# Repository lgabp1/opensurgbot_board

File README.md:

# opensurgbot_board

Submodule of [opensurgbot](https://github.com/lgabp1/opensurgbot).

Board design for the opensurgbot first prototype.

## About

The opensurgbot was temporarily named _deehli_, and the board design has not been updated since the name change. Thus, the kicad files and the board name still refer to _deehli_.

## Known issues (vB-1.03)
- Several trace connections were forgotten in version vB-1.03

## Versions
### v0.1

### v1.0

### v1.02

### vB-1.01

### vB-1.03

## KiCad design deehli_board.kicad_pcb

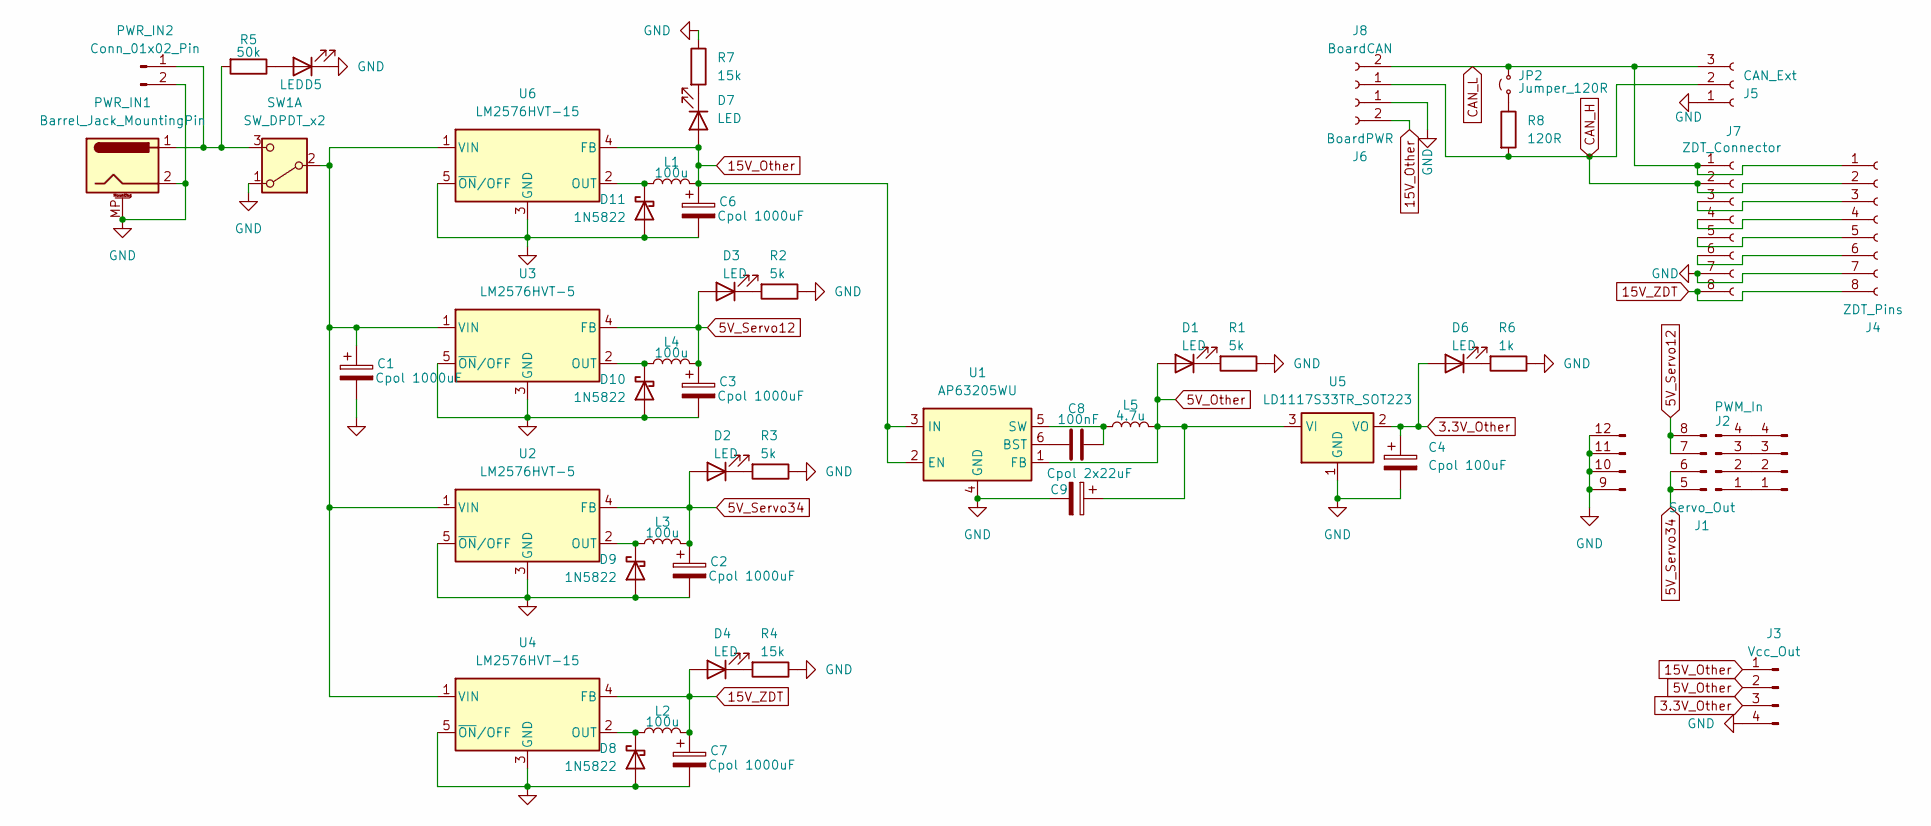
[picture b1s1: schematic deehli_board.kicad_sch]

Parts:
C1, C2, C3, C6, C7: Cpol 1000uF; CP_Radial_D10.0mm_P5.00mm
C4: Cpol 100uF; CP_Radial_D6.3mm_P2.50mm
C8: 100nF; C_0805_2012Metric_Pad1.18x1.45mm_HandSolder
C9: Cpol 2x22uF; CP_Radial_D6.3mm_P2.50mm
D1, D2, D3, D4, D5, D6, D7: LED; LED_0805_2012Metric_Pad1.15x1.40mm_HandSolder
D8, D9, D10, D11: 1N5822; D_DO-201AD_P15.24mm_Horizontal
J1: Servo_Out; PinHeader_3x04_P2.54mm_Vertical
J2: PWM_In; PinHeader_1x04_P2.54mm_Vertical
J3: Vcc_Out; PinSocket_1x04_P2.54mm_Vertical
J4: ZDT_Pins; PinSocket_1x08_P2.54mm_Horizontal
J5: CAN_Ext; TerminalBlock_Xinya_XY308-2.54-3P_1x03_P2.54mm_Horizontal
J6: BoardPWR; TerminalBlock_Xinya_XY308-2.54-2P_1x02_P2.54mm_Horizontal
J7: ZDT_Connector; JST_EH_S8B-EH_1x08_P2.50mm_Horizontal
J8: BoardCAN; TerminalBlock_Xinya_XY308-2.54-2P_1x02_P2.54mm_Horizontal
JP2: Jumper_120R; PinHeader_1x02_P2.54mm_Vertical
L1, L2, L3, L4: 100u; L_Radial_D8.7mm_P5.00mm_Fastron_07HCP
L5: 4.7u; L_Radial_D8.7mm_P5.00mm_Fastron_07HCP
PWR_IN1: Barrel_Jack_MountingPin; BarrelJack_CUI_PJ-063AH_Horizontal
PWR_IN2: Conn_01x02_Pin; PinHeader_1x02_P2.54mm_Vertical
R1, R2, R3: 5k; R_0805_2012Metric_Pad1.20x1.40mm_HandSolder
R4, R7: 15k; R_0805_2012Metric_Pad1.20x1.40mm_HandSolder
R5: 50k; R_0805_2012Metric_Pad1.20x1.40mm_HandSolder
R6: 1k; R_0805_2012Metric_Pad1.20x1.40mm_HandSolder
R8: 120R; R_0805_2012Metric_Pad1.20x1.40mm_HandSolder
SW1: SW_DPDT_x2; SW_Toggle_Blue_wSlots
U1: AP63205WU; TSOT-23-6
U2, U3: LM2576HVT-5; TO-220-5_Vertical
U4, U6: LM2576HVT-15; TO-220-5_Vertical
U5: LD1117S33TR_SOT223; SOT-223-3_TabPin2

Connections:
3.3V_Other: C4.1, D6.2 (A), J3.3, U5.2 (VO)
5V_Other: C9.1, D1.2 (A), J3.2, L5.2, U1.1 (FB), U5.3 (VI)
5V_Servo12: C3.1, D3.2 (A), J1.7, J1.8, L4.2, U3.4 (FB)
5V_Servo34: C2.1, D2.2 (A), J1.5, J1.6, L3.2, U2.4 (FB)
15V_Other: C6.1, D7.2 (A), J3.1, J6.2, L1.2, U1.2 (EN), U1.3 (IN), U6.4 (FB)
15V_ZDT: C7.1, D4.2 (A), J4.8, J7.8, L2.2, U4.4 (FB)
CAN_H: J4.2, J5.2, J7.2, J8.1, R8.2
CAN_L: J4.1, J5.3, J7.1, J8.2, JP2.2 (B)
GND: C1.2, C2.2, C3.2, C4.2, C6.2, C7.2, C9.2, D5.1 (K), D8.2 (A), D9.2 (A), D10.2 (A), D11.2 (A), J1.9, J1.10, J1.11, J1.12, J3.4, J4.7, J5.1, J6.1, J7.7, PWR_IN1.2, PWR_IN1.MP (MountPin), PWR_IN2.2, R1.1, R2.1, R3.1, R4.1, R6.1, R7.1, SW1.1 (A), U1.4 (GND), U2.3 (GND), U2.5 (~ON/OFF), U3.3 (GND), U3.5 (~ON/OFF), U4.3 (GND), U4.5 (~ON/OFF), U5.1 (GND), U6.3 (GND), U6.5 (~ON/OFF)
unnamed: D1.1 (K), R1.2
unnamed: D2.1 (K), R3.2
unnamed: D3.1 (K), R2.2
unnamed: D4.1 (K), R4.2
unnamed: D5.2 (A), R5.1
unnamed: D6.1 (K), R6.2
unnamed: D7.1 (K), R7.2
unnamed: D8.1 (K), L2.1, U4.2 (OUT)
unnamed: D9.1 (K), L3.1, U2.2 (OUT)
unnamed: D10.1 (K), L4.1, U3.2 (OUT)
unnamed: D11.1 (K), L1.1, U6.2 (OUT)
unnamed: J1.1, J2.1
unnamed: J1.2, J2.2
unnamed: J1.3, J2.3
unnamed: J1.4, J2.4
unnamed: J4.3, J7.3
unnamed: J4.4, J7.4
unnamed: J4.5, J7.5
unnamed: J4.6, J7.6
unnamed: JP2.1 (A), R8.1
unnamed: PWR_IN1.1, PWR_IN2.1, R5.2, SW1.3 (C)
unnamed: C1.1, SW1.2 (B), U2.1 (VIN), U3.1 (VIN), U4.1 (VIN), U6.1 (VIN)
unnamed: C8.1, U1.6 (BST)
unnamed: C8.2, L5.1, U1.5 (SW)

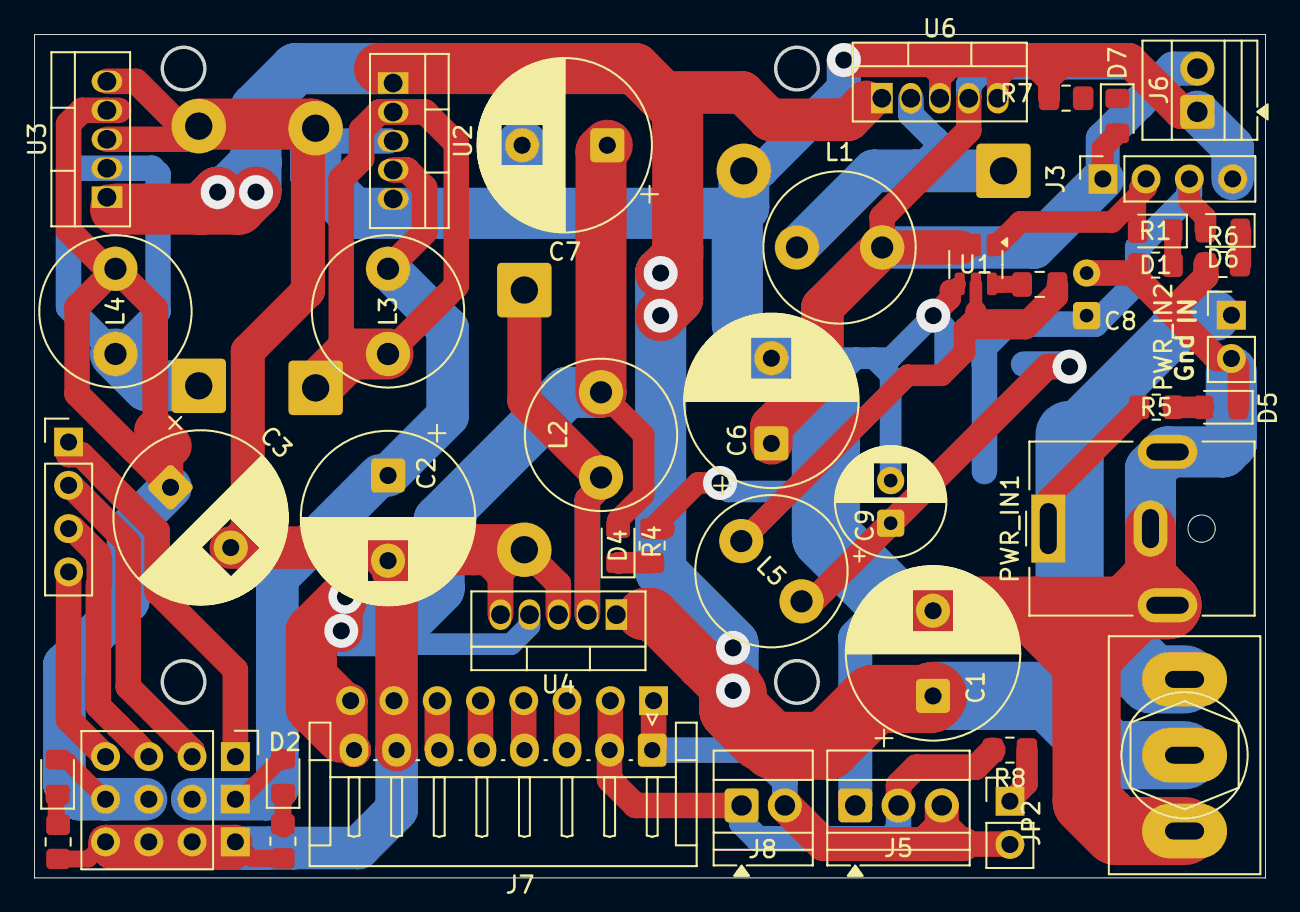
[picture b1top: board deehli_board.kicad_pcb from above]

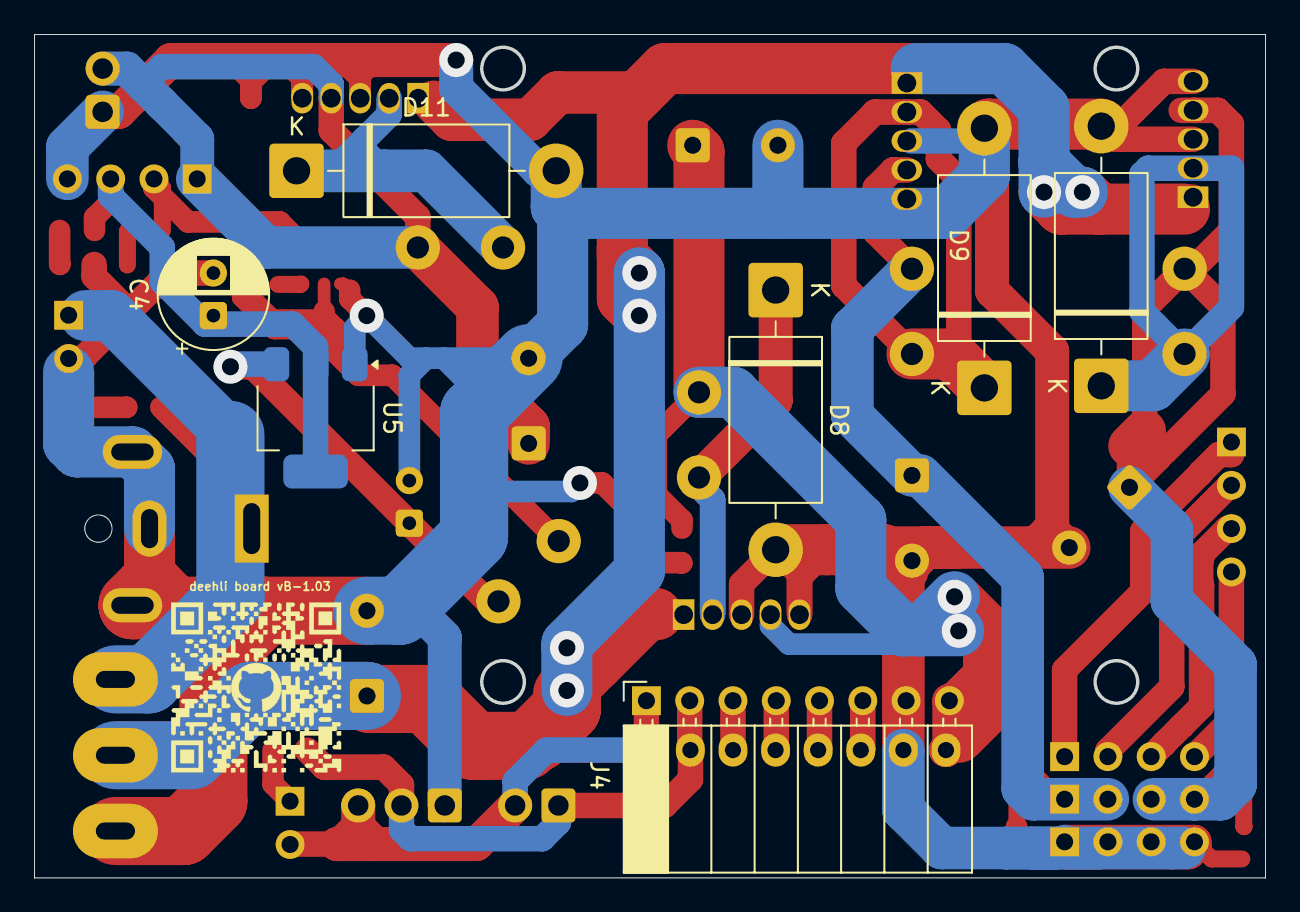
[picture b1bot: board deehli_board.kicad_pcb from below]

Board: 2 copper layers, 72.2 x 49.5 mm, 50 parts (7 on the bottom side), 33 nets.

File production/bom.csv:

Designator,Footprint,Quantity,Value,LCSC Part #
"C1, C2, C3, C6, C7",CP_Radial_D10.0mm_P5.00mm,5,Cpol 1000uF,
C4,CP_Radial_D6.3mm_P2.50mm,1,Cpol 100uF,
C8,0805,1,100nF,
C9,CP_Radial_D6.3mm_P2.50mm,1,Cpol 2x22uF,
"D1, D2, D3, D4, D5, D6, D7",0805,7,LED,
"D10, D11, D8, D9",D_DO-201AD_P15.24mm_Horizontal,4,1N5822,
J1,PinHeader_3x04_P2.54mm_Vertical,1,Servo_Out,
J2,PinHeader_1x04_P2.54mm_Vertical,1,PWM_In,
J3,PinSocket_1x04_P2.54mm_Vertical,1,Vcc_Out,
J4,PinSocket_1x08_P2.54mm_Horizontal,1,ZDT_Pins,
J5,TerminalBlock_Xinya_XY308-2.54-3P_1x03_P2.54mm_Horizontal,1,CAN_Ext,
J6,TerminalBlock_Xinya_XY308-2.54-2P_1x02_P2.54mm_Horizontal,1,BoardPWR,
J7,JST_EH_S8B-EH_1x08_P2.50mm_Horizontal,1,ZDT_Connector,
J8,TerminalBlock_Xinya_XY308-2.54-2P_1x02_P2.54mm_Horizontal,1,BoardCAN,
JP2,PinHeader_1x02_P2.54mm_Vertical,1,Jumper_120R,
"L1, L2, L3, L4",L_Radial_D8.7mm_P5.00mm_Fastron_07HCP,4,100u,
L5,L_Radial_D8.7mm_P5.00mm_Fastron_07HCP,1,4.7u,
PWR_IN1,BarrelJack_CUI_PJ-063AH_Horizontal,1,Barrel_Jack_MountingPin,
PWR_IN2,PinHeader_1x02_P2.54mm_Vertical,1,Conn_01x02_Pin,
"R1, R2, R3",0805,3,5k,
"R4, R7",0805,2,15k,
R5,0805,1,50k,
R6,0805,1,1k,
R8,0805,1,120R,
SW1,SW_Toggle_Blue_wSlots,1,SW_DPDT_x2,
U1,TSOT-23-6,1,AP63205WU,
"U2, U3",TO-220-5_Vertical,2,LM2576HVT-5,
"U4, U6",TO-220-5_Vertical,2,LM2576HVT-15,
U5,SOT-223-3_TabPin2,1,LD1117S33TR_SOT223,

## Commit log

2025-06-26 v1.01 cleaned up
2025-06-27 v1.02
2025-06-27 vB-1.00
2025-06-27 vB-1.01
2025-07-01 vB-1.01 export
2025-07-04 Begin vB-1.02
2025-07-04 VB-1.02
2025-07-10 vB-1.03
2025-07-10 Added exports for vB-1.03
2025-08-08 Renamed repository and changed README.md accordingly.
